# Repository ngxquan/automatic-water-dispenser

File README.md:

This is a project from intro to engineering (Haui university)

Components list:
- 7805 * 1
- 100uF capacitor * 2
- 104 ceramic capacitor * 2
- 100 ohm resistor * 1
- 330 ohm reistor * 4 
- 10k resistor * 2 
- 100k resistor * 1k
- Ir receiver * 1
- Ir transmitter * 1
- Ic lm393 * 1
- 50k potentiometer * 1 
- Irfz44 * 1 (i choose irfz44 because i avaible in my room)
- Relay 5vdc * 1
- flyback diode * 1
- 12v pump 
- 12v adapter 

How is works?
- IR Emission & Reflection: The IR transmitter continuously emits an infrared beam. Placing a cup in front of the sensor reflects this beam back toward the IR receiver.
- Signal Detection: As the IR receiver absorbs the reflected light, its internal resistance drops (photoconductive effect), pulling down the voltage at the sensor node.
- Threshold Comparison (LM393): The LM393 comparator compares this changing sensor voltage with a fixed reference voltage ($V_{ref}$) adjusted via an onboard potentiometer.
- Pump Activation & Calibration: When the sensor voltage falls below $V_{ref}$, the LM393 switches its output state to activate the water pump. Turning the potentiometer changes $V_{ref}$, allowing precise calibration of the sensing range.

Schematic:

Prototype on breadboard:

short demo: [youtube link](https://youtu.be/mfwWYmZwk9E)

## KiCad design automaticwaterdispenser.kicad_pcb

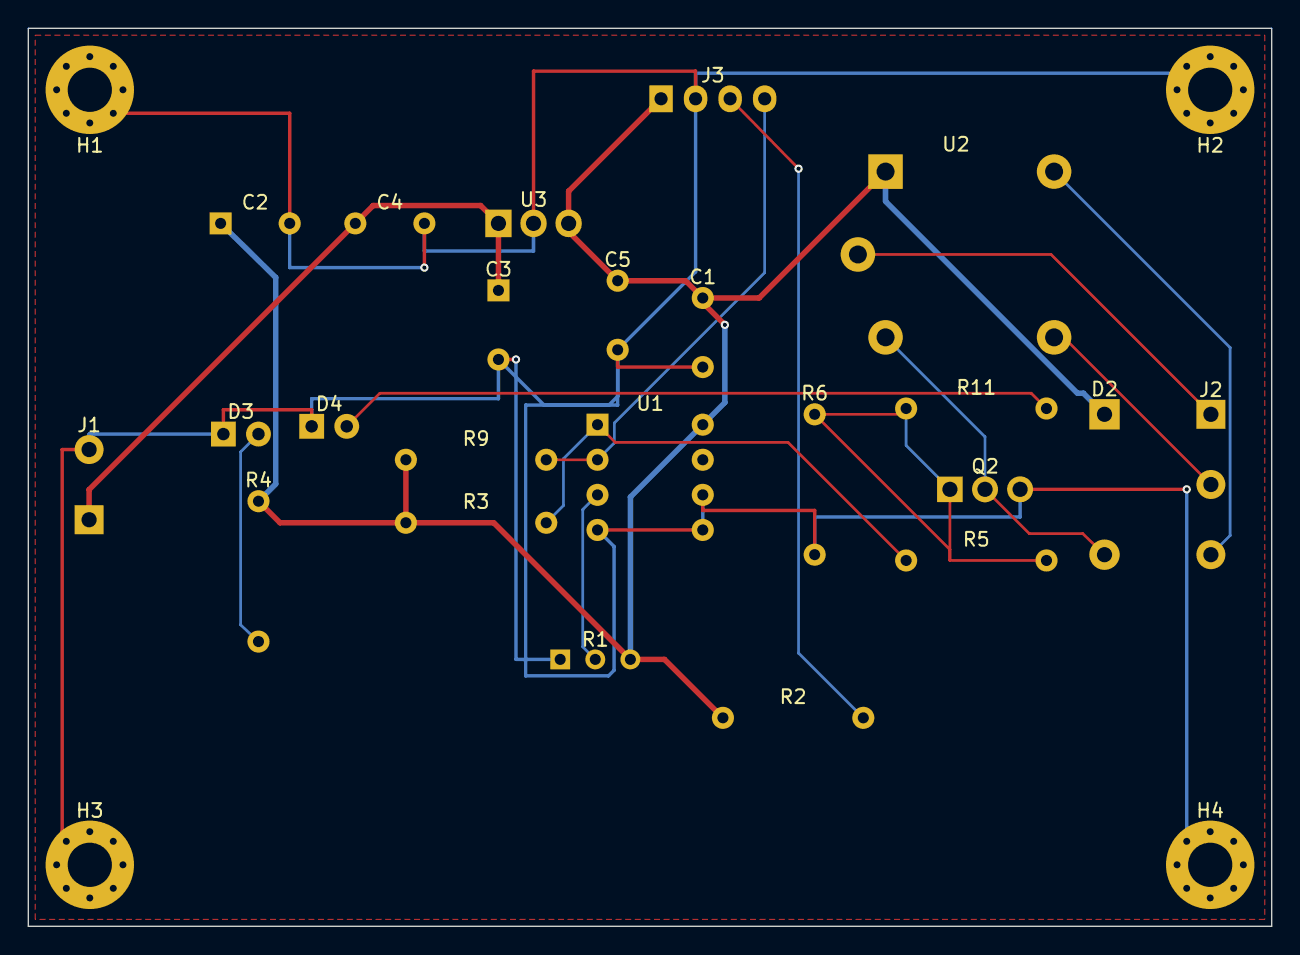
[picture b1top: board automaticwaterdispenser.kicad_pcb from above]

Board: 2 copper layers, 90.0 x 65.0 mm, 27 parts (0 on the bottom side), 14 nets.

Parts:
C1, C4, C5: 100nF; C_Disc_D5.0mm_W2.5mm_P5.00mm
C2: 100uF 16V; CP_Radial_D8.0mm_P5.00mm
C3: 100uF 25V; CP_Radial_D8.0mm_P5.00mm
D2: DO-41_SOD81; D_DO-41_SOD81_P10.16mm_Horizontal
D3: Red 3mm; LED_D3.0mm
D4: Green 3mm; LED_D3.0mm
H1, H2, H3, H4: M3; MountingHole_3.2mm_M3_Pad_Via
J1: 2P 5.08mm; TerminalBlock_RND_205-00232_1x02_P5.08mm_Horizontal
J2: 3P 5.08mm; TerminalBlock_RND_205-00233_1x03_P5.08mm_Horizontal
J3: JST_XH_B4B-XH-A(LF)(SN); JST_XH_B4B-XH-A_1x04_P2.50mm_Vertical
Q2: IRFZ44N; TO-220-3
R1: 50k; Potentiometer_Bourns_3386W_Horizontal
R2, R4, R9, R11: 330; R_Axial_DIN0207_L6.3mm_D2.5mm_P10.16mm_Horizontal
R3: 10kΩ; R_Axial_DIN0207_L6.3mm_D2.5mm_P10.16mm_Horizontal
R5: 100Ω; R_Axial_DIN0207_L6.3mm_D2.5mm_P10.16mm_Horizontal
R6: 100kΩ; R_Axial_DIN0207_L6.3mm_D2.5mm_P10.16mm_Horizontal
U1: LM393N; DIP-8_W7.62mm
U2: JQC-3FF-005-1Z; Relay_SPDT_Hongfa_JQC-3FF_0XX-1Z
U3: L7805CV; TO-220-3_Vertical

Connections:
5V: C1.1, C2.1, C5.1, D2.1 (K), J3.1, R1.3, R2.1, R3.1, R4.1, R9.1, U1.8 (V+), U2.A1, U3.3 (OUT)
COMP_OUT: R3.2, R5.1, U1.1
GND: C1.2, C2.2, C3.2, C4.2, C5.2, D3.1, D4.1, H1.1, H2.1, H3.1, H4.1, J1.2, J3.2, Q2.3 (Source), R1.1, R6.2, U1.4 (V-), U1.5 (+), U1.6 (-), U3.2 (GND)
IR_LED_A: J3.3, R2.2
LED1_A: D3.2, R4.2
LED_STATUS_A: D4.2, R11.2
PUMP1_GATE: Q2.1 (Gate), R5.2, R6.1, R11.1
PUMP1_SW: D2.2 (A), Q2.2 (Drain), U2.A2
R1_W: R1.2, U1.3 (+)
RELAY_COM: J2.1, U2.11
RELAY_NC: J2.3, U2.12
RELAY_NO: J2.2, U2.14
SENSE: J3.4, R9.2, U1.2 (-)
VIN: C3.1, C4.1, J1.1, U3.1 (IN)
